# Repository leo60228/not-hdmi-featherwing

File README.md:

# Not HDMI Featherwing

A Featherwing (intended for the Adafruit Feather RP2040, though it might work with the Sparkfun Thing Plus RP2040 too) for DVI video output.

A compatible PicoDVI fork is at https://github.com/leo60228/PicoDVI/tree/not-hdmi-featherwing.

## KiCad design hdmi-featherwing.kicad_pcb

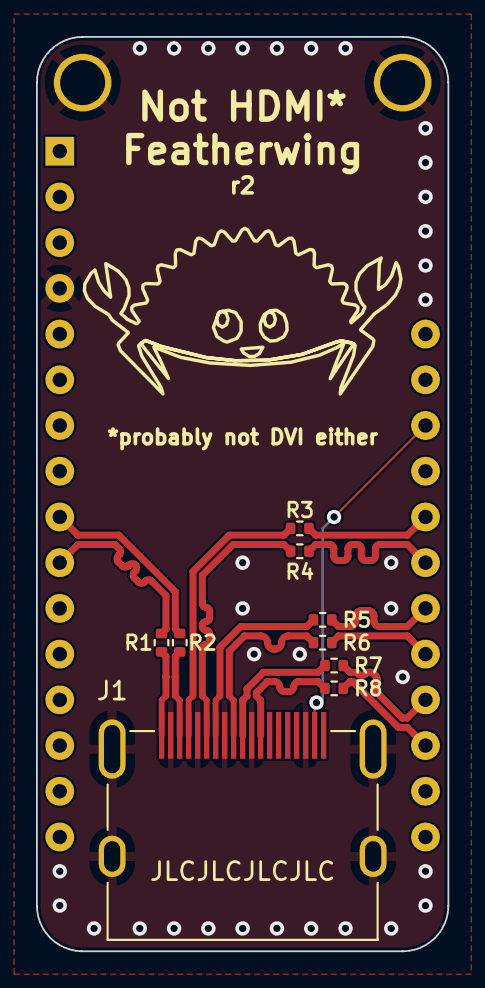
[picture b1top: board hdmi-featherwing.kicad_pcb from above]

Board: 2 copper layers, 22.9 x 50.8 mm, 13 parts (0 on the bottom side), 18 nets.

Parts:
A1: Adafruit_Feather_Generic; Adafruit_Feather_WithMountingHoles
Ferris: G*****; Ferris
H1**, H2**: MountingHole_2.5mm_Pad
J1: HDMI_A; KH-HDMI-19P-Cu
R1, R2, R3, R4, R5, R6, R7, R8: 300; R_0402_1005Metric

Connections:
+5V: A1.26 (USB), J1.18 (+5V)
/CK+: J1.10 (CK+), R7.2
/CK-: J1.12 (CK-), R8.2
/D0+: J1.7 (D0+), R5.2
/D0-: J1.9 (D0-), R6.2
/D1+: J1.4 (D1+), R3.2
/D1-: J1.6 (D1-), R4.2
/D2+: J1.1 (D2+), R1.2
/D2-: J1.3 (D2-), R2.2
/WING_CK+: A1.20 (D1), R7.1
/WING_CK-: A1.19 (D0), R8.1
/WING_D0+: A1.22 (D3), R5.1
/WING_D0-: A1.21 (D2), R6.1
/WING_D1+: A1.24 (D5), R3.1
/WING_D1-: A1.23 (D4), R4.1
/WING_D2+: A1.10 (A5), R1.1
/WING_D2-: A1.9 (A4), R2.1
GND: A1.4 (GND), H1**.1, H2**.1, J1.2 (D2S), J1.5 (D1S), J1.8 (D0S), J1.11 (CKS), J1.17 (GND), J1.SH

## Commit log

2021-03-29 init
2021-03-29 create project
2021-03-29 Add HDMI footprint
2021-03-29 Improve footprint
2021-03-29 Add HDMI connector to schematic
2021-03-29 Add Feather to schematic
2021-03-29 Assign footprints
2021-03-29 Create PCB
2021-03-29 Remove Feather edges
2021-03-29 Add Feather Edge.Cuts
2021-03-29 Add DRC rules
2021-03-29 Fix silkscreen DRC
2021-03-29 Add CK resistors
2021-03-29 Label differential pair nets
2021-03-29 Route resistors
2021-03-29 Fix violations
2021-03-29 Silkscreen
2021-03-29 Add product codes for assembly
2021-03-29 Ignore fab
2021-03-29 Plot
2021-03-29 Generate BOM
2021-03-29 Add JLCJLCJLCJLC silkscreen
2021-03-29 Fix HDMI origin
2021-04-17 add readme
2021-09-05 upd8
2021-09-05 0402 resistors
2021-09-05 clear pcb
2021-09-05 add smt hdmi connector footprint
2021-09-05 use smt hdmi connector footprint
2021-09-05 add footprints to pcb
2021-09-05 update silkscreen for r2
2021-09-05 add DVI netclass
2021-09-05 fix reference designators
2021-09-05 route diffpairs
2021-09-05 make silkscreen labels visible
2021-09-05 pour both layers
2021-09-05 ground vias
2021-09-05 ignore silkscreen warnings
2021-09-05 fix drc
2021-09-05 route 5V
2021-09-05 add more vias
2021-09-05 300 ohm resistors
2021-09-05 Add LCSC property
2021-09-05 better position HDMI_A
2021-09-05 account for Feather in length matching
2021-09-06 better route resistors
2021-09-06 fix silkscreen
2021-09-06 add extra ground vias
2021-09-06 prep for fab
